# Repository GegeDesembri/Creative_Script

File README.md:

<h1 align="center">Hi 👋, I'm Gege Desembri</h1>
<h3 align="center">A passionate fullstack developer from Indonesia</h3>

- 🌱 I’m currently learning **Native Programing**

- 📝 I regularly write articles on [https://gescripter.blogspot.com/](https://gescripter.blogspot.com/)

- 💬 Ask me about **C, C++, Linux Shell, and Python**

- 📫 How to reach me **GegeDesembri.643.UM@gmail.com**

<h3 align="left">Connect with me:</h3>
<p align="left">

</p>

<h3 align="left">Languages and Tools:</h3>
<p align="left">        </p>

<p>&nbsp;</p>

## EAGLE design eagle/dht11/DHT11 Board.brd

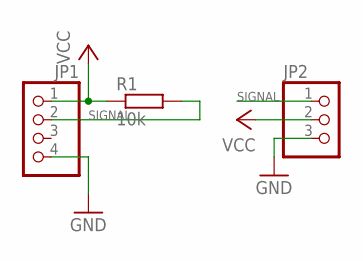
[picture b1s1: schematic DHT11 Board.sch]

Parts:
JP1: PINHD-1X4; 1X04
JP2: PINHD-1X3; 1X03
R1: 10k; 0204/7

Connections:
GND: JP1.4, JP2.3
SIGNAL: JP1.2, JP2.1, R1.2
VCC: JP1.1, JP2.2, R1.1

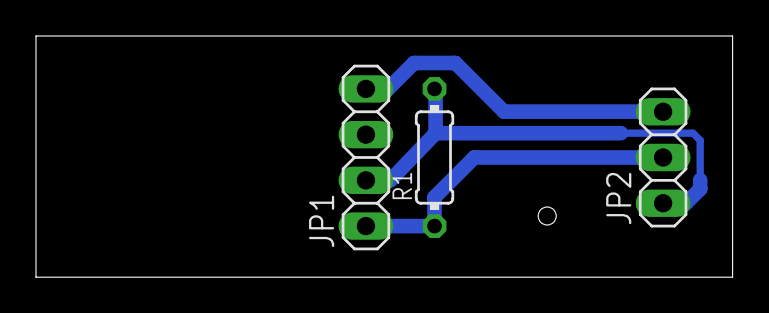
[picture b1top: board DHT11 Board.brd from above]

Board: 2 copper layers, 38.7 x 13.4 mm, 3 parts (0 on the bottom side), 3 nets.

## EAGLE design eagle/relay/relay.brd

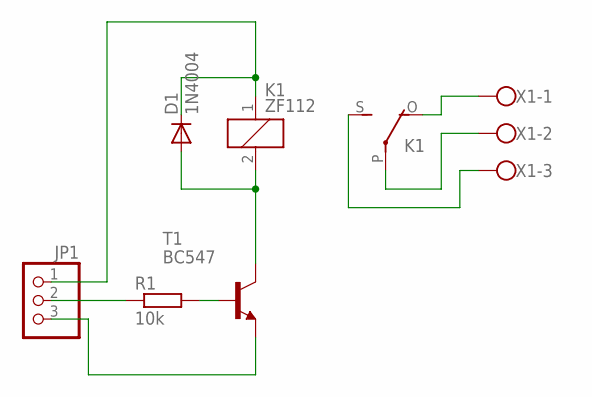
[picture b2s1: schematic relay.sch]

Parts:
D1: 1N4004; DO41-10
JP1: PINHD-1X3; 1X03
K1: ZF112
R1: 10k; 0204/7
T1: BC547; TO92
X1: W237-103

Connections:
unnamed: D1.C, JP1.1, K1.1
unnamed: D1.A, K1.2, T1.3 (C)
unnamed: R1.2, T1.2 (B)
unnamed: K1.O, X1.1
unnamed: K1.S, X1.3
unnamed: K1.P, X1.2
unnamed: JP1.3, T1.1 (E)
unnamed: JP1.2, R1.1

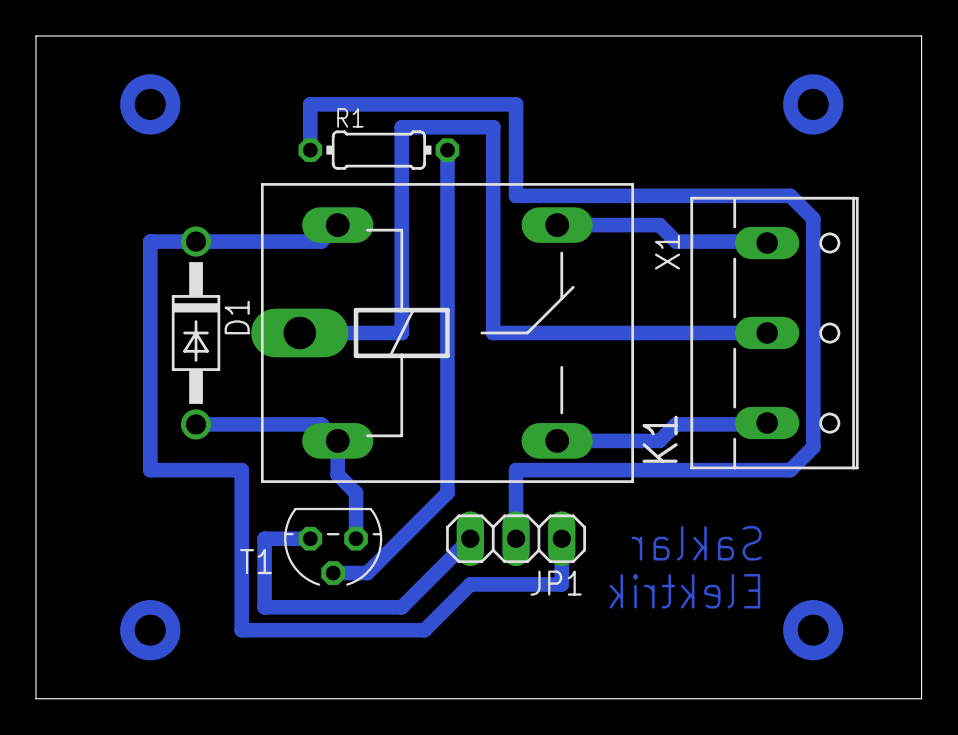
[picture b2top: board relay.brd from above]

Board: 2 copper layers, 49.2 x 36.8 mm, 6 parts (0 on the bottom side), 8 nets.

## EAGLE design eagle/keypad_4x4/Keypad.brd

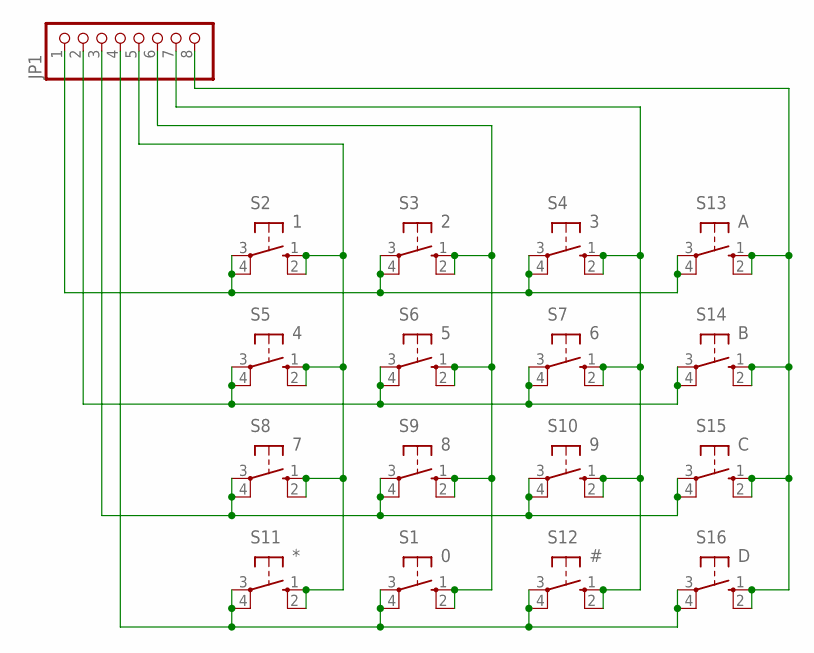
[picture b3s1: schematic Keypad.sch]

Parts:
JP1: PINHD-1X8; 1X08
S1: 0; B3F-10XX
S2: 1; B3F-10XX
S3: 2; B3F-10XX
S4: 3; B3F-10XX
S5: 4; B3F-10XX
S6: 5; B3F-10XX
S7: 6; B3F-10XX
S8: 7; B3F-10XX
S9: 8; B3F-10XX
S10: 9; B3F-10XX
S11: *; B3F-10XX
S12: #; B3F-10XX
S13: A; B3F-10XX
S14: B; B3F-10XX
S15: C; B3F-10XX
S16: D; B3F-10XX

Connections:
C1: JP1.5, S2.1 (S), S2.2 (S1), S5.1 (S), S5.2 (S1), S8.1 (S), S8.2 (S1), S11.1 (S), S11.2 (S1)
C2: JP1.6, S1.1 (S), S1.2 (S1), S3.1 (S), S3.2 (S1), S6.1 (S), S6.2 (S1), S9.1 (S), S9.2 (S1)
C3: JP1.7, S4.1 (S), S4.2 (S1), S7.1 (S), S7.2 (S1), S10.1 (S), S10.2 (S1), S12.1 (S), S12.2 (S1)
C4: JP1.8, S13.1 (S), S13.2 (S1), S14.1 (S), S14.2 (S1), S15.1 (S), S15.2 (S1), S16.1 (S), S16.2 (S1)
R1: JP1.1, S2.3, S2.4 (P1), S3.3, S3.4 (P1), S4.3, S4.4 (P1), S13.3, S13.4 (P1)
R2: JP1.2, S5.3, S5.4 (P1), S6.3, S6.4 (P1), S7.3, S7.4 (P1), S14.3, S14.4 (P1)
R3: JP1.3, S8.3, S8.4 (P1), S9.3, S9.4 (P1), S10.3, S10.4 (P1), S15.3, S15.4 (P1)
R4: JP1.4, S1.3, S1.4 (P1), S11.3, S11.4 (P1), S12.3, S12.4 (P1), S16.3, S16.4 (P1)

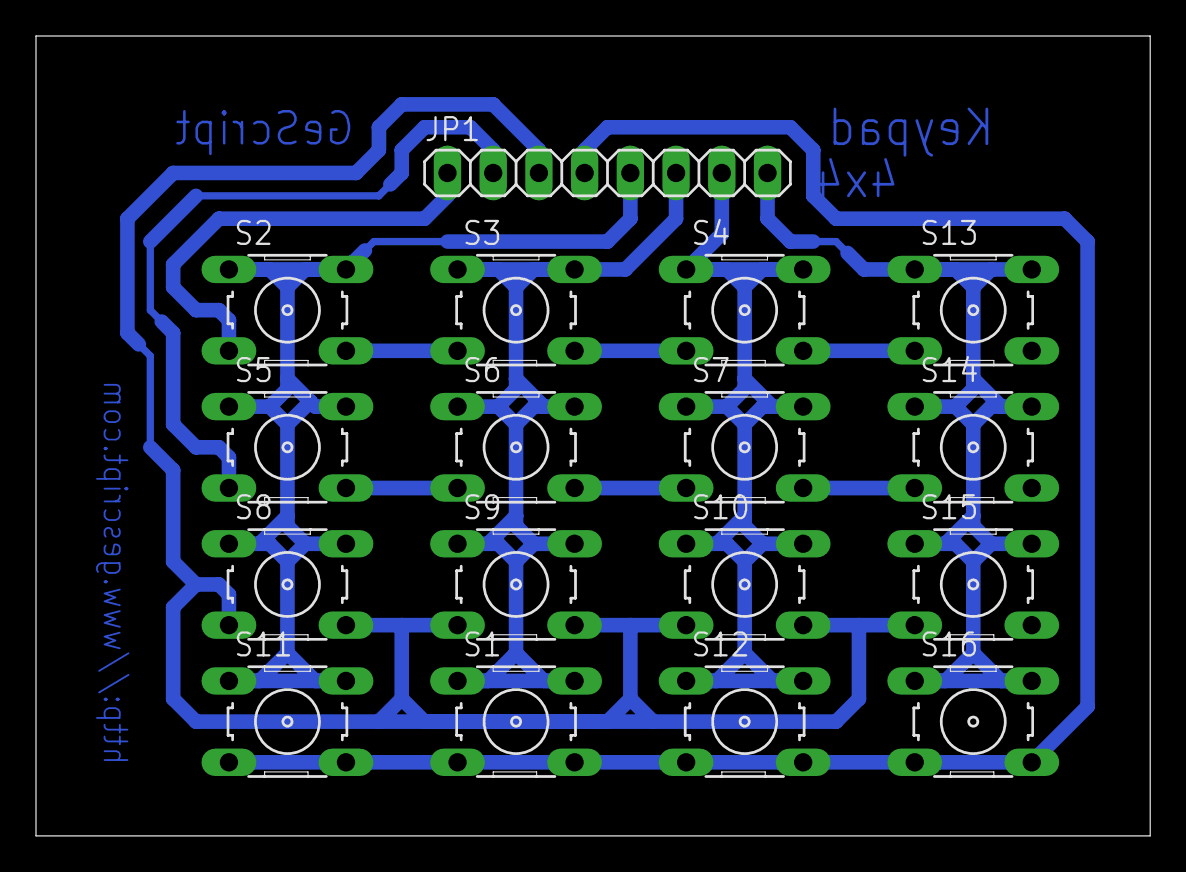
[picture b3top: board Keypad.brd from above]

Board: 2 copper layers, 61.9 x 44.4 mm, 17 parts (0 on the bottom side), 8 nets.

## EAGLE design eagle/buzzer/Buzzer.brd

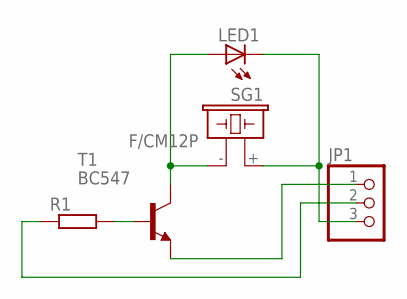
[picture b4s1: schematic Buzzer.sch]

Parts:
JP1: PINHD-1X3; 1X03
LED1: LED3MM
R1: R-EU_0204/7; 0204/7
SG1: F/CM12P
T1: BC547; TO92

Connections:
unnamed: R1.2, T1.2 (B)
unnamed: LED1.A, SG1.- (2), T1.3 (C)
unnamed: JP1.2, R1.1
unnamed: JP1.1, T1.1 (E)
unnamed: JP1.3, LED1.K (C), SG1.+ (1)

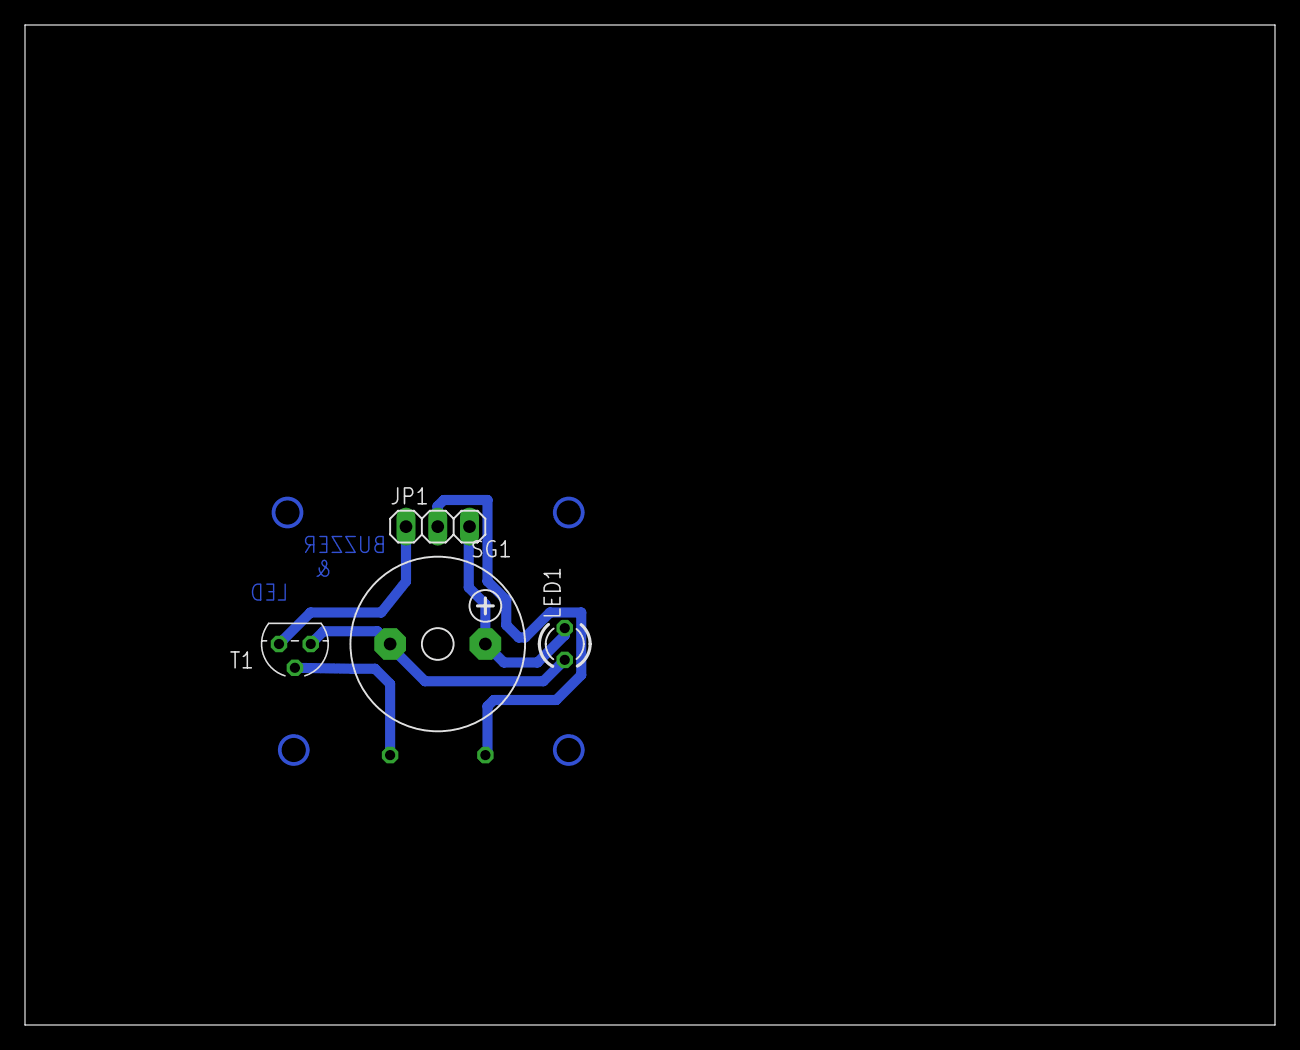
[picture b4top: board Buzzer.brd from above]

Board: 2 copper layers, 100.0 x 80.0 mm, 5 parts (1 on the bottom side), 5 nets.

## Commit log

2021-06-22 Cek Commit
2021-06-22 aria2c & teamspeak3 upload
2021-06-22 revisi total aria2-core
2021-06-23 Edit Readme
2021-06-23 Readme updated
2021-06-23 readme update
2021-06-23 py and index
2021-06-24 bulk adding
2021-06-24 import
2021-07-02 js-html-python
2021-07-02 variable-js
2021-07-02 arithmetic-js
2021-10-17 ccminer onboot
2021-10-17 tutoral JS
2021-10-17 syntax
2021-10-17 duplicate
2021-10-17 add details
2021-10-17 github markdown refer
2021-10-17 markdown preview
2021-10-17 references
2021-10-17 delete
2022-08-23 CryptoJS
2022-08-23 TEST JS
